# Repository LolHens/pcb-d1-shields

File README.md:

# pcb-d1-shields

Miscellaneous shields for the d1 mini.

## Shields
- d1 stepper shield
- d1 relay module shield

## License
This project uses the Apache 2.0 License. See the file called LICENSE.

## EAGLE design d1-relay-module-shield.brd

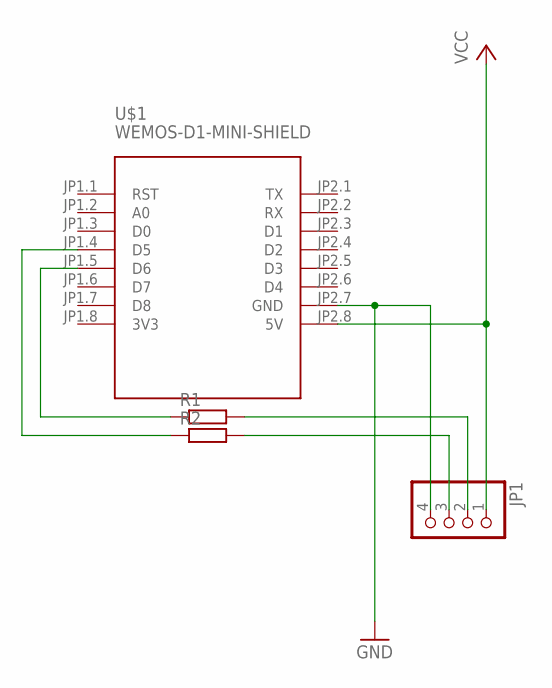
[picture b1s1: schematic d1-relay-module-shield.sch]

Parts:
JP1: PINHD-1X4; 1X04
R1, R2: R-EU_R0603; R0603
U$1: WEMOS-D1-MINI-SHIELD

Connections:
3V3: U$1.JP1.8 (3V3)
GND: JP1.4, U$1.JP2.7 (GND)
unnamed: JP1.2, R1.2
unnamed: JP1.3, R2.2
unnamed: R1.1, U$1.JP1.5 (D6)
unnamed: R2.1, U$1.JP1.4 (D5)
VCC: JP1.1, U$1.JP2.8 (5V)

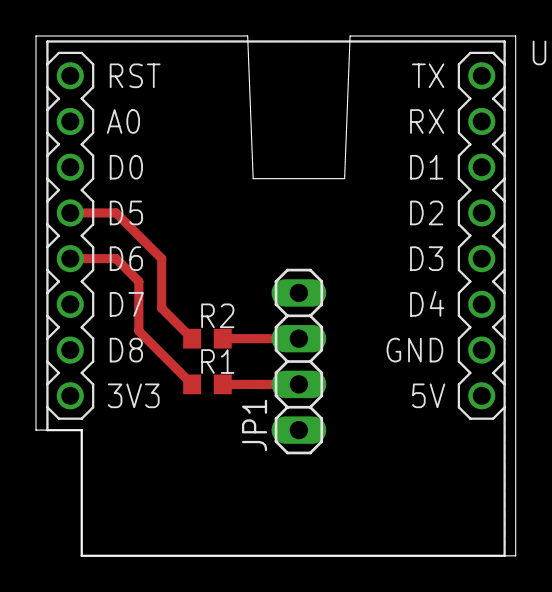
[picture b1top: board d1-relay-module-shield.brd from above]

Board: 2 copper layers, 26.6 x 28.9 mm, 4 parts (0 on the bottom side), 6 nets.

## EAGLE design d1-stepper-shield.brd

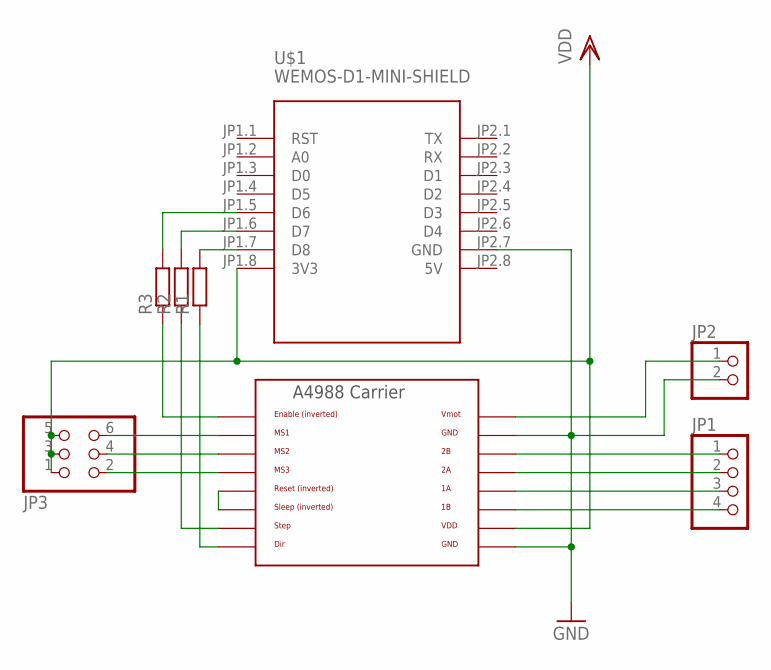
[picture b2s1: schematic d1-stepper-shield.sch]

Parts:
JP1: PINHD-1X4; 1X04
JP2: PINHD-1X2; 1X02
JP3: PINHD-2X3; 2X03
R1, R2, R3: R-EU_R0603; R0603
U$1: WEMOS-D1-MINI-SHIELD
U$2: A4988BREAKOUT

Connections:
5V: U$1.JP2.8 (5V)
GND: JP2.2, U$1.JP2.7 (GND), U$2.GND, U$2.GND@0 (GND)
unnamed: JP1.1, U$2.2B
unnamed: JP1.2, U$2.2A
unnamed: JP1.3, U$2.1A
unnamed: JP1.4, U$2.1B
unnamed: JP3.6, U$2.MS1
unnamed: JP2.1, U$2.VMOT
unnamed: U$2.RST, U$2.SLP (SLEEP)
unnamed: JP3.2, U$2.MS3
unnamed: JP3.4, U$2.MS2
unnamed: R1.1, U$2.DIR
unnamed: R2.1, U$2.STEP
unnamed: R1.2, U$1.JP1.7 (D8)
unnamed: R2.2, U$1.JP1.6 (D7)
unnamed: R3.2, U$1.JP1.5 (D6)
unnamed: R3.1, U$2.EN
VDD: JP3.1, JP3.3, JP3.5, U$1.JP1.8 (3V3), U$2.VDD

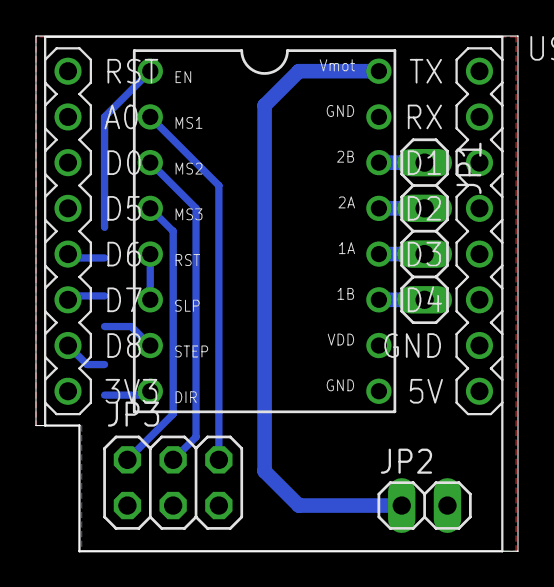
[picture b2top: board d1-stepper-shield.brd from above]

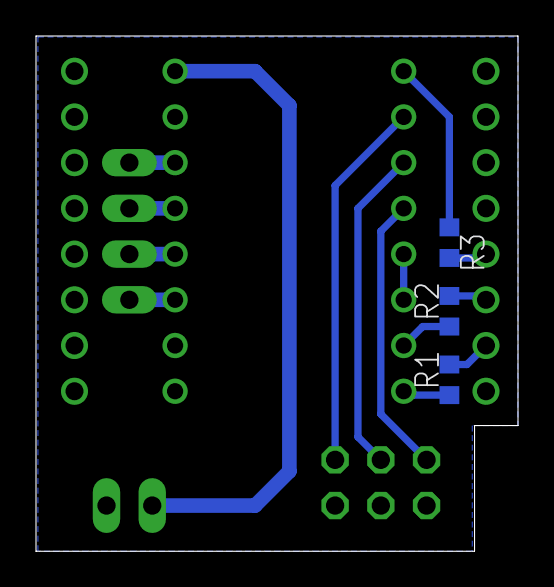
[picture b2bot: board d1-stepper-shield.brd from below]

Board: 2 copper layers, 26.8 x 28.6 mm, 8 parts (3 on the bottom side), 17 nets.

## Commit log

2020-08-02 added files
2020-08-02 LICENSE
2020-08-02 added libs
2020-08-02 d1-relay-module-shield
2020-08-17 align d1 with edge of relay board and add cutout for jumper

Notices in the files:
README.md:
Apache License 2.0
parts and their libraries:
diy-modules: Released under the Creative Commons Attribution 4.0 International License: http://creativecommons.org/licenses/by/4.0
